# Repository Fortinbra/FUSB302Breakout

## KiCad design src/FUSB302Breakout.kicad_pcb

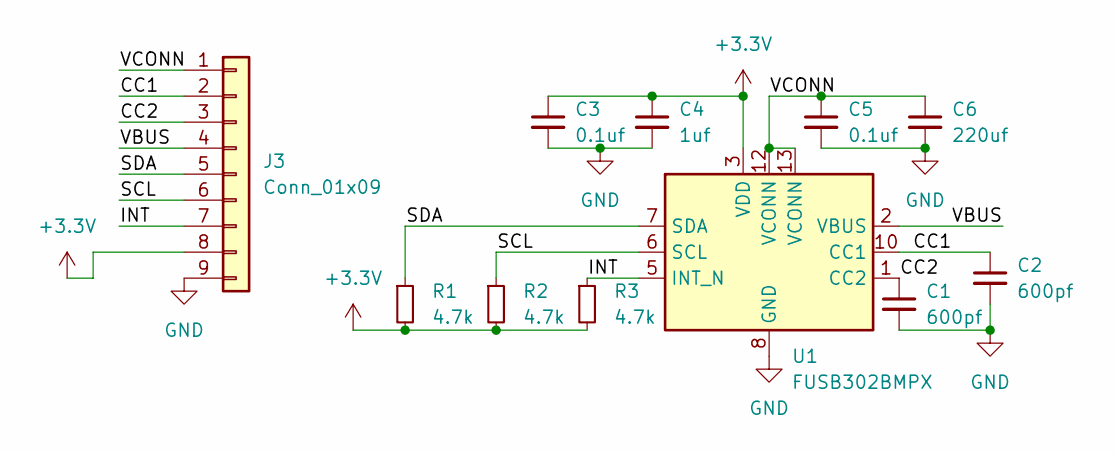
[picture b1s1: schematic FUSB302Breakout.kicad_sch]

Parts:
C1, C2: 600pf; CP_Radial_D4.0mm_P1.50mm
C3, C5: 0.1uf; C_0603_1608Metric_Pad1.08x0.95mm_HandSolder
C4: 1uf; C_0603_1608Metric_Pad1.08x0.95mm_HandSolder
C6: 220uf; C_0603_1608Metric_Pad1.08x0.95mm_HandSolder
J3: Conn_01x09; PinHeader_1x09_P2.54mm_Vertical
R1, R2, R3: 4.7k; C_0603_1608Metric_Pad1.08x0.95mm_HandSolder
U1: FUSB302BMPX; WQFN-14-1EP_2.5x2.5mm_P0.5mm_EP1.45x1.45mm

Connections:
+3.3V: C3.1, C4.1, J3.8, R1.2, R2.2, R3.2, U1.3 (VDD), U1.4 (VDD)
/CC1: C2.1, J3.2, U1.10 (CC1), U1.11 (CC1)
/CC2: C1.1, J3.3, U1.1 (CC2), U1.14 (CC2)
/INT: J3.7, R3.1, U1.5 (INT_N)
/SCL: J3.6, R2.1, U1.6 (SCL)
/SDA: J3.5, R1.1, U1.7 (SDA)
/VBUS: J3.4, U1.2 (VBUS)
/VCONN: C5.1, C6.1, J3.1, U1.12 (VCONN), U1.13 (VCONN)
GND: C1.2, C2.2, C3.2, C4.2, C5.2, C6.2, J3.9, U1.8 (GND), U1.9 (GND), U1.15 (GND)

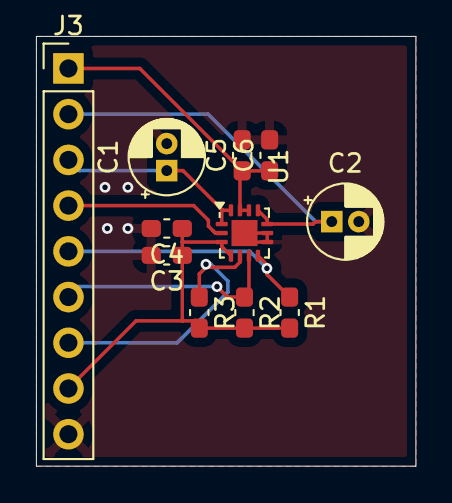
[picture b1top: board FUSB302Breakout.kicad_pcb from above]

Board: 2 copper layers, 21.1 x 23.9 mm, 11 parts (0 on the bottom side), 9 nets.
